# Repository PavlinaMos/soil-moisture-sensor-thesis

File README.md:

# Soil Moisture Sensor Thesis

This repository contains the soil-moisture measurement project:

- ESP32 firmware for impedance measurement, Wi-Fi provisioning, and Arduino Cloud publishing.
- KiCad schematic and PCB sources for the measurement hardware.
- R scripts used to analyze the soil samples examined in impedance spectroscopy 
- The editable LaTeX thesis and its figures.

## Repository layout

```text
.
|-- firmware/                           ESP32 PlatformIO project
|   |-- include/                        Cloud definitions and local secrets
|   |-- src/                            Application code
|   `-- platformio.ini                  Board, framework, and library settings        
|-- analysis/impedance_spectroscopy/    R analysis scripts and usage notes
|-- PCB/kicad/soil-board/               KiCad schematic, PCB, and project files
|-- thesis/                             LaTeX sources, bibliography, and figures
```

## Firmware overview

The firmware targets an ESP32 NodeMCU-32S. It drives the measurement circuit,
calculates resistance (`RP`) and capacitance (`CP`), and publishes the results
to Arduino Cloud.

WiFiManager handles Wi-Fi setup without needing hard-coded network credentials. Known
networks are stored in the ESP32's non-volatile memory. At startup, the device
tries to connect to saved networks and opens a setup portal when none can
be reached.

### Analog parts

1. LTC6268
2. AD8130
3. AD8066
4. ADG733

### Modules

1. AD9833 waveform generator
2. ADS1115 ADC
3. AD8302 gain-phase detector

## Firmware development environment

Install:

1. [Visual Studio Code](https://code.visualstudio.com/)
2. The PlatformIO IDE extension for VS Code
3. The CP210x USB-to-UART driver if the ESP32 does not appear as a Windows COM port

Open the `firmware/` folder in VS Code. PlatformIO reads the exact toolchain and
library versions pinned in `firmware/platformio.ini`.

## Configure private secrets

Copy `firmware/include/arduino_secrets.h`, then add the matching Arduino Cloud
device key. Don't share its contents.

```cpp
#pragma once

#define SECRET_SSID ""
#define SECRET_PASS ""
#define SECRET_DEVICE_KEY "paste-your-Arduino-Cloud-device-key-here"
```

WiFiManager does not use `SECRET_SSID` or `SECRET_PASS` during normal
operation, they remain for compatibility. `SECRET_DEVICE_KEY` is required for
Arduino Cloud authentication.

## Build and upload the firmware

In VS Code, use the PlatformIO buttons in the bottom status bar:

- **Check mark**: build the project.
- **Right arrow**: upload the firmware to the ESP32.
- **Plug icon**: open the serial monitor.

The first build downloads and compiles dependencies, so it takes longer. 

To upload:

1. Connect the NodeMCU-32S using a USB data cable.
2. Confirm that Windows assigns it a COM port.
3. Click the PlatformIO **Upload** arrow.
4. If the board does not enter download mode automatically, hold **BOOT** until writing starts.

The serial monitor uses **115200 baud** and displays measurements, Wi-Fi state,
and Arduino Cloud connection messages.

## Wi-Fi provisioning

When no saved network can connect, the ESP32 creates the protected setup access
point `ESP32-Meter-Setup`. Connect with password `configure-me` and use the
captive portal (or `192.168.4.1`) to select a 2.4 GHz Wi-Fi network. The current
implementation stores up to five profiles; when the list is full, slot 0 is
replaced.

## Arduino Cloud

After joining Wi-Fi, the ESP32 connects to Arduino Cloud and publishes the
measurements periodically. The dashboard shows current `RP` and `CP` values and
their time history. Cloud retention depends on the Arduino Cloud plan.

## Hardware design

Open `PCB/kicad/soil-board/SoilBoard.kicad_pro` in KiCad. See the
[PCB notes](PCB/kicad/soil-board/README.md) for more info.

## Data analysis

The R scripts are under `analysis/impedance_spectroscopy/`. They cover
mean-squared error, Nyquist plots, sampled Nyquist comparisons, and
phase/impedance plots.

## Thesis

The thesis source is under `thesis/`. Its main document is `thesis/main.tex`
and it uses pdfLaTeX.

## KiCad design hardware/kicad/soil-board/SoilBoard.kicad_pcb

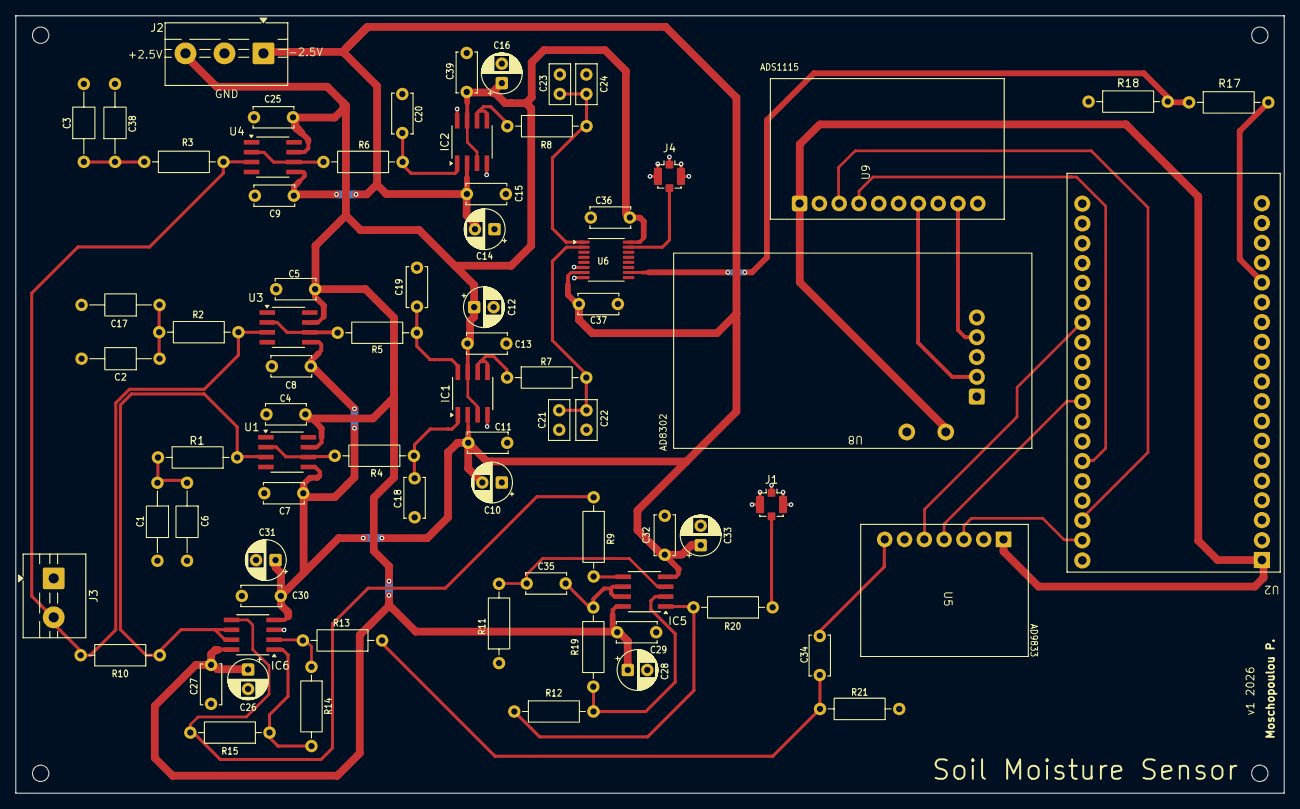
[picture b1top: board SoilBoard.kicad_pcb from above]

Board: 2 copper layers, 162.7 x 99.7 mm, 79 parts (0 on the bottom side), 40 nets.

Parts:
C1, C2, C3, C6, C17, C38: 2p; C_Axial_L3.8mm_D2.6mm_P10.00mm_Horizontal
C4, C5, C7, C8, C9, C11, C13, C15, C25, C27, C29, C30, C32, C34, C36, C37, C39: 0.1u; C_Disc_D5.0mm_W2.5mm_P5.00mm
C10, C12, C14, C16: 10u; CP_Radial_D5.0mm_P2.50mm
C18, C19, C20: 560p; C_Disc_D5.0mm_W2.5mm_P5.00mm
C21, C22, C23, C24: 100p; C_Disc_D5.0mm_W2.5mm_P2.50mm
C26, C28, C31, C33: 4.7u; CP_Radial_D5.0mm_P2.50mm
C35: 6.8p; C_Disc_D5.0mm_W2.5mm_P5.00mm
IC1, IC2: AD8130ARM; PowerIntegrations_SO-8
IC5, IC6: AD8066ARMZ; PowerIntegrations_SO-8
J1, J4: Conn_01x01_Pin; U.FL_Molex_MCRF_73412-0110_Vertical
J2: Screw_Terminal_01x03; TerminalBlock_MaiXu_MX126-5.0-03P_1x03_P5.00mm
J3: Screw_Terminal_01x02; TerminalBlock_MaiXu_MX126-5.0-02P_1x02_P5.00mm
MH1, MH2, MH3, MH4: MountingHole; MountingHole_2.1mm
R1, R2, R3, R4, R5, R6, R7, R8, R10, R20: 47; R_Axial_DIN0207_L6.3mm_D2.5mm_P10.16mm_Horizontal
R9, R15: 27; R_Axial_DIN0207_L6.3mm_D2.5mm_P10.16mm_Horizontal
R11: 1.3k; R_Axial_DIN0207_L6.3mm_D2.5mm_P10.16mm_Horizontal
R12, R17, R19: 2.2k; R_Axial_DIN0207_L6.3mm_D2.5mm_P10.16mm_Horizontal
R13: 6.8k; R_Axial_DIN0207_L6.3mm_D2.5mm_P10.16mm_Horizontal
R14: 10k; R_Axial_DIN0207_L6.3mm_D2.5mm_P10.16mm_Horizontal
R18: 4.7k; R_Axial_DIN0207_L6.3mm_D2.5mm_P10.16mm_Horizontal
R21: 1k; R_Axial_DIN0207_L6.3mm_D2.5mm_P10.16mm_Horizontal
U1, U3, U4: LTC6268_THT; PowerIntegrations_SO-8
U2: ESP32
U5: AD9833
U6: ADG733BRU; TSSOP-16_4.4x5mm_P0.65mm
U8: AD8302
U9: ADS115; ADS1115

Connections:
/3.3: U2.1 (3.3), U5.1 (Vcc), U8.1 (Vcc), U9.1 (Vcc)
/D+: IC6.6 (-IN2), IC6.7 (VOUT2), R1.1, R10.1, U1.3 (+IN)
/D-: J3.2, R2.1, R3.1, R10.2, U3.3 (+IN), U4.3 (+IN)
/FSYNC1: U2.26 (GPIO4), U5.5 (FSYNC)
/SCL: U2.36 (GPIO22), U9.3 (SCL)
/SDA: U2.33 (GPIO21), U9.4 (SDA)
/VDDS: C34.2, U5.7 (OUT)
/Vcontrol: R17.1, R18.2, U6.10
/Vreference: J1.1 (Pin_1_1), R20.1
/Vsignals: J4.1 (Pin_1_1), U6.15
/signal A: C23.1, C24.1, R8.2, U6.1
/signal B: C21.1, C22.1, R7.2, U6.2
GND: C1.2, C2.2, C3.2, C4.2, C5.2, C6.2, C7.2, C8.2, C9.2, C10.1, C11.1, C12.2, C13.2, C14.1, C15.1, C16.2, C17.2, C18.2, C19.2, C20.2, C21.2, C22.2, C23.2, C24.2, C25.2, C26.2, C27.2, C28.2, C29.2, C30.2, C31.2, C32.2, C33.2, C36.2, C37.2, C38.2, C39.2, IC1.4 (REF), IC2.4 (REF), IC2.8 (-IN), IC6.3 (+IN1), J1.2, J2.2, J3.1, J4.2, R11.1, R18.1, R21.1, U2.14 (GND), U2.32 (GND), U2.38 (GND), U5.2 (DGND), U5.6 (AGND), U6.6 (~EN), U6.8 (GND), U8.2 (GND), U8.5 (AGND), U8.9 (AGND), U9.2 (GND), U9.5 (ADDR)
unnamed: C1.1, C6.1, R1.2
unnamed: C3.1, C38.1, R3.2
unnamed: C2.1, C17.1, R2.2
unnamed: C34.1, R13.1, R21.2
unnamed: C18.1, IC1.1 (+IN), R4.1
unnamed: C19.1, IC1.8 (-IN), R5.1
unnamed: IC1.5 (FB), IC1.6 (OUT), R7.1
unnamed: C20.1, IC2.1 (+IN), R6.1
unnamed: IC2.5 (FB), IC2.6 (OUT), R8.1
unnamed: C35.1, IC5.3 (+IN1), R11.2
unnamed: IC5.5 (+IN2), R9.2
unnamed: IC5.2 (-IN1), R12.2, R19.1
unnamed: C35.2, IC5.6 (-IN2), IC5.7 (VOUT2), R19.2
unnamed: IC5.1 (VOUT1), R12.1, R20.2
unnamed: IC6.5 (+IN2), R9.1, R15.2
unnamed: IC6.2 (-IN1), R13.2, R14.1
unnamed: IC6.1 (VOUT1), R14.2, R15.1
unnamed: R4.2, U1.2 (-IN), U1.6 (Vout)
unnamed: R17.2, U2.15 (GPIO13)
unnamed: U2.30 (GPIO18), U5.4 (SCLK)
unnamed: U2.37 (GPIO23), U5.3 (SDATA)
unnamed: R5.2, U3.2 (-IN), U3.6 (Vout)
unnamed: R6.2, U4.2 (-IN), U4.6 (Vout)
unnamed: U8.6 (VMAG), U9.7 (A0)
unnamed: U8.8 (VPHS), U9.9 (A2)
VCC: C4.1, C5.1, C12.1, C13.1, C16.1, C25.1, C26.1, C27.1, C28.1, C29.1, C36.1, C39.1, IC1.3 (~PD), IC1.7 (+VS), IC2.3 (~PD), IC2.7 (+VS), IC5.8 (+VS), IC6.8 (+VS), J2.3, U1.7 (V+), U3.7 (V+), U4.7 (V+), U6.16 (VDD)
VDD: C7.1, C8.1, C9.1, C10.2, C11.2, C14.2, C15.2, C30.1, C31.1, C32.1, C33.1, C37.1, IC1.2 (-VS), IC2.2 (-VS), IC5.4 (-VS), IC6.4 (-VS), J2.1, U1.5 (V-), U3.5 (V-), U4.5 (V-), U6.7 (VSS)
